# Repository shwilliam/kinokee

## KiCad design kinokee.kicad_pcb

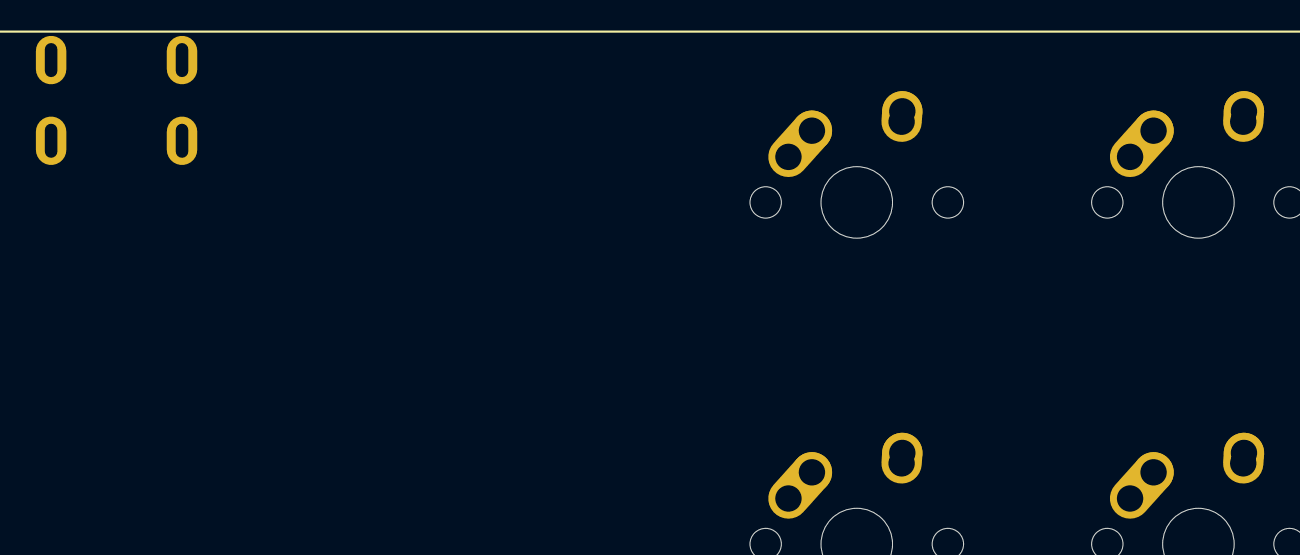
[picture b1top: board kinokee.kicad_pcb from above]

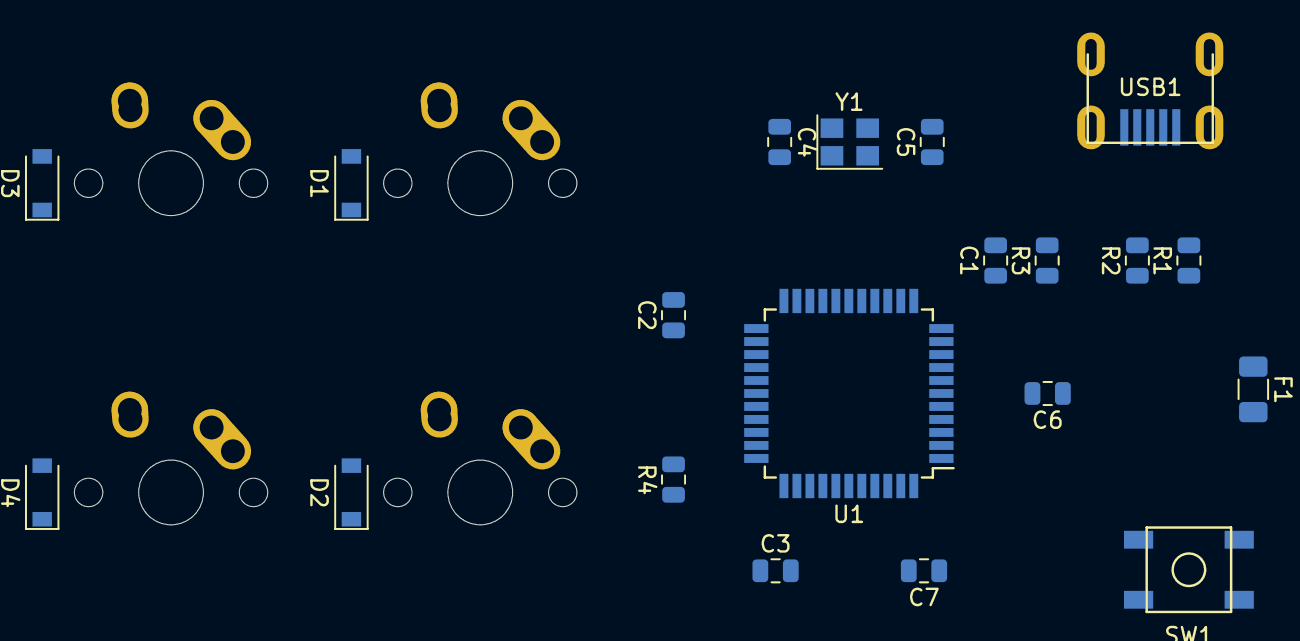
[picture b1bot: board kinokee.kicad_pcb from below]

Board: 2 copper layers, 24 parts (20 on the bottom side), 20 nets, no tracks yet.

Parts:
C1, C2, C3: 0.1uF; C_0805_2012Metric
C4, C5: 22pF; C_0805_2012Metric
C6: 1uF; C_0805_2012Metric
C7: 10uF; C_0805_2012Metric
D1, D2, D3, D4: D_Small; D_SOD-123
F1: 500mA; Fuse_1206_3216Metric
MX1, MX2, MX3, MX4: MX-NoLED; MX-1U-NoLED
R1, R2: 22; R_0805_2012Metric
R3, R4: 10k; R_0805_2012Metric
SW1: SW_Push; SKQG-1155865
U1: ATmega32U4-AU; TQFP-44_10x10mm_P0.8mm
USB1: Molex-0548190589
Y1: 16MHz; Crystal_SMD_3225-4Pin_3.2x2.5mm

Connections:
+5V: C1.1, C2.1, C3.1, C7.1, F1.1, R3.1, U1.2, U1.7, U1.14, U1.24, U1.34, U1.44
COL0: MX1.1, MX3.1
COL1: MX2.1, MX4.1
D+: R2.2, USB1.3
D-: R1.2, USB1.4
GND: C1.2, C2.2, C3.2, C4.1, C5.1, C6.2, C7.2, R4.1, SW1.1, U1.5, U1.15, U1.23, U1.35, U1.43, USB1.1, Y1.2, Y1.4
unnamed: C4.2, U1.17, Y1.1
unnamed: C5.2, U1.16, Y1.3
unnamed: C6.1, U1.6
unnamed: D1.2, MX1.2
unnamed: D2.2, MX3.2
unnamed: D3.2, MX2.2
unnamed: D4.2, MX4.2
unnamed: R1.1, U1.3
unnamed: R2.1, U1.4
unnamed: R3.2, SW1.2, U1.13
unnamed: R4.2, U1.33
ROW0: D1.1, D3.1
ROW1: D2.1, D4.1
VCC: F1.2, USB1.5

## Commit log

2021-12-12 init
2021-12-12 init pcb
2021-12-12 add basic keeb component libs as submodules
2021-12-12 add basic keeb libs as symbols
2021-12-12 set up mcu
2021-12-12 add 2x2 matrix and usb to schematic
2021-12-12 assign footprints to schematic
2021-12-12 fix capacitor footprint
2021-12-12 sketch component placement
2021-12-27 cleanup and rename
2021-12-28 route and fill
2021-12-28 add gerbers
